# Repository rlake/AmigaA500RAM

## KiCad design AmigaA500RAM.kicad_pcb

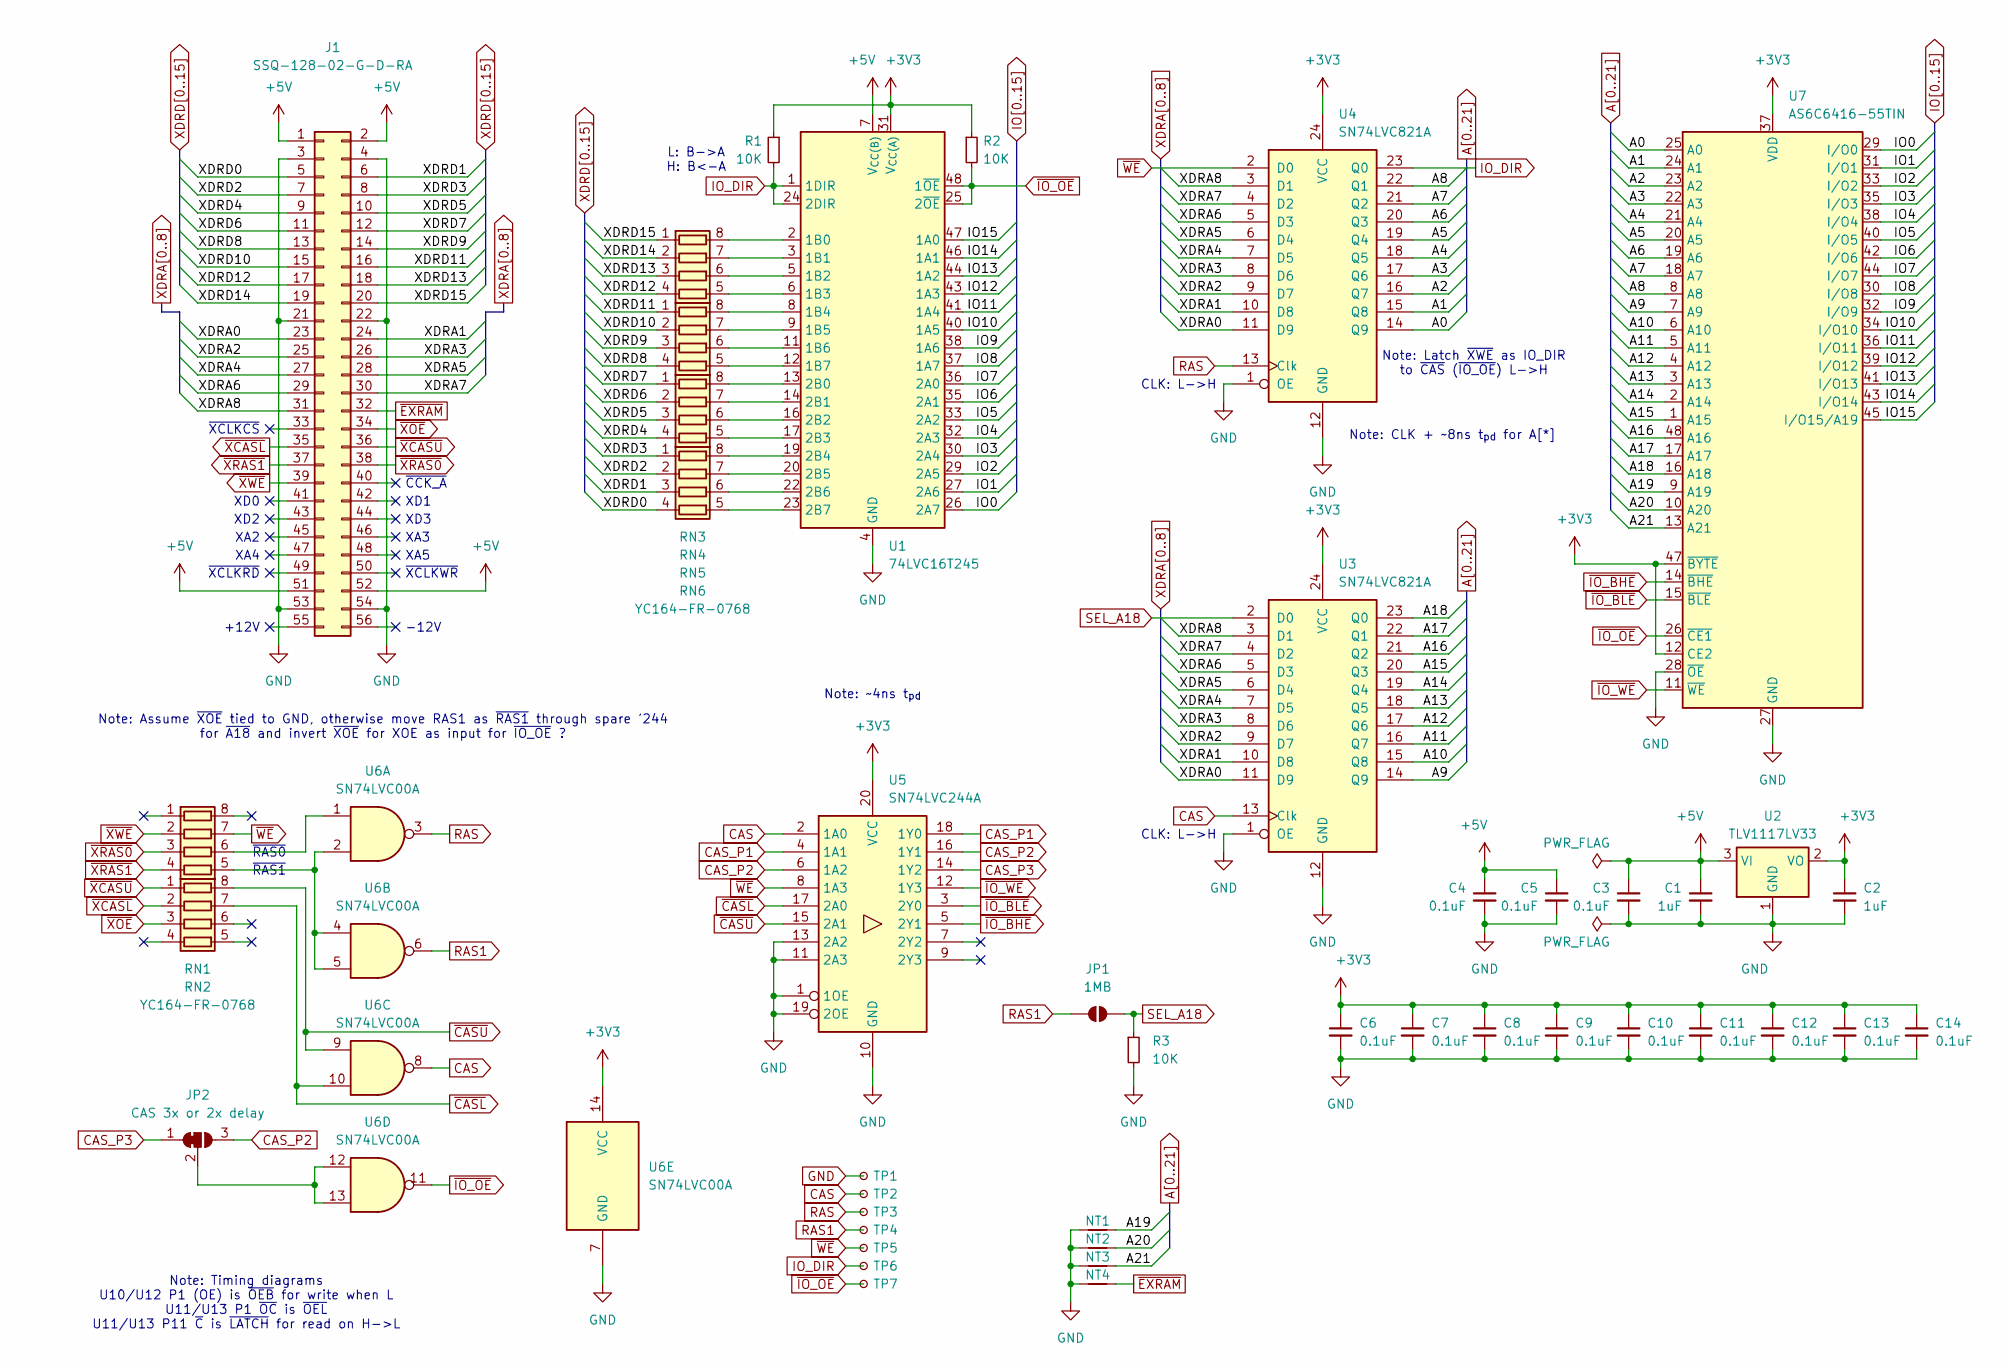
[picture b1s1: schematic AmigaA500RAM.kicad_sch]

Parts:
C1, C2: 1uF; C_0805_2012Metric
C3, C4, C5, C6, C7, C8, C9, C10, C11, C12, C13, C14: 0.1uF; C_0805_2012Metric
J1: SSQ-128-02-G-D-RA; PinSocket_2x28_P2.54mm_Horizontal_A501
JP1: 1MB; SolderJumper-2_P1.3mm_Open_RoundedPad1.0x1.5mm
JP2: CAS 3x or 2x delay; SolderJumper-3_P1.3mm_Bridged2Bar12_RoundedPad1.0x1.5mm
NT1, NT2, NT3, NT4: NetTie_2; NetTie-2_SMD_Pad0.5mm
R1, R2, R3: 10K; R_0805_2012Metric
RN1, RN2, RN3, RN4, RN5, RN6: YC164-FR-0768; R_Array_Convex_4x0603
TP1: TestPoint_Small; TestPoint_Keystone_5016_Compact
TP2, TP3, TP4, TP5, TP6, TP7: TestPoint_Small; TestPoint_Pad_D1.0mm
U1: 74LVC16T245; TSSOP-48_6.1x12.5mm_P0.5mm
U2: TLV1117LV33; SOT-223-3_TabPin2
U3, U4: SN74LVC821A; TSSOP-24_4.4x7.8mm_P0.65mm
U5: SN74LVC244A; TSSOP-20_4.4x6.5mm_P0.65mm
U6: SN74LVC00A; TSSOP-14_4.4x5mm_P0.65mm
U7: AS6C6416-55TIN; TSOP-I-48_18.4x12mm_P0.5mm

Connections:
+3V3: C2.1, C6.1, C7.1, C8.1, C9.1, C10.1, C11.1, C12.1, C13.1, C14.1, R1.1, R2.1, U1.31 (V_{CC(A)}), U1.42 (V_{CC(A)}), U2.2 (VO), U3.24 (VCC), U4.24 (VCC), U5.20 (VCC), U6.14 (VCC), U7.12 (CE2), U7.37 (VDD), U7.47 (~BYTE)
+5V: C1.1, C3.1, C4.1, C5.1, J1.1, J1.2, J1.51, J1.52, U1.7 (V_{CC(B)}), U1.18 (V_{CC(B)}), U2.3 (VI)
A0: U4.14 (Q9), U7.25 (A0)
A1: U4.15 (Q8), U7.24 (A1)
A2: U4.16 (Q7), U7.23 (A2)
A3: U4.17 (Q6), U7.22 (A3)
A4: U4.18 (Q5), U7.21 (A4)
A5: U4.19 (Q4), U7.20 (A5)
A6: U4.20 (Q3), U7.19 (A6)
A7: U4.21 (Q2), U7.18 (A7)
A8: U4.22 (Q1), U7.8 (A8)
A9: U3.14 (Q9), U7.7 (A9)
A10: U3.15 (Q8), U7.6 (A10)
A11: U3.16 (Q7), U7.5 (A11)
A12: U3.17 (Q6), U7.4 (A12)
A13: U3.18 (Q5), U7.3 (A13)
A14: U3.19 (Q4), U7.2 (A14)
A15: U3.20 (Q3), U7.1 (A15)
A16: U3.21 (Q2), U7.48 (A16)
A17: U3.22 (Q1), U7.17 (A17)
A18: U3.23 (Q0), U7.16 (A18)
A19: NT1.2, U7.9 (A19)
A20: NT2.2, U7.10 (A20)
A21: NT3.2, U7.13 (A21)
CAS: TP2.1, U3.13 (Clk), U5.2 (1A0), U6.8
CAS_P1: U5.4 (1A1), U5.18 (1Y0)
CAS_P2: JP2.3 (B), U5.6 (1A2), U5.16 (1Y1)
CAS_P3: JP2.1 (A), U5.14 (1Y2)
GND: C1.2, C2.2, C3.2, C4.2, C5.2, C6.2, C7.2, C8.2, C9.2, C10.2, C11.2, C12.2, C13.2, C14.2, J1.3, J1.4, J1.21, J1.22, J1.53, J1.54, NT1.1, NT2.1, NT3.1, NT4.1, R3.2, TP1.1, U1.4 (GND), U1.10 (GND), U1.15 (GND), U1.21 (GND), U1.28 (GND), U1.34 (GND), U1.39 (GND), U1.45 (GND), U2.1 (GND), U3.1 (OE), U3.12 (GND), U4.1 (OE), U4.12 (GND), U5.1 (1OE), U5.10 (GND), U5.11 (2A3), U5.13 (2A2), U5.19 (2OE), U6.7 (GND), U7.27 (GND), U7.28 (~OE), U7.46 (GND)
IO0: U1.26 (2A7), U7.29 (I/O0)
IO1: U1.27 (2A6), U7.31 (I/O1)
IO2: U1.29 (2A5), U7.33 (I/O2)
IO3: U1.30 (2A4), U7.35 (I/O3)
IO4: U1.32 (2A3), U7.38 (I/O4)
IO5: U1.33 (2A2), U7.40 (I/O5)
IO6: U1.35 (2A1), U7.42 (I/O6)
IO7: U1.36 (2A0), U7.44 (I/O7)
IO8: U1.37 (1A7), U7.30 (I/O8)
IO9: U1.38 (1A6), U7.32 (I/O9)
IO10: U1.40 (1A5), U7.34 (I/O10)
IO11: U1.41 (1A4), U7.36 (I/O11)
IO12: U1.43 (1A3), U7.39 (I/O12)
IO13: U1.44 (1A2), U7.41 (I/O13)
IO14: U1.46 (1A1), U7.43 (I/O14)
IO15: U1.47 (1A0), U7.45 (I/O15/A19)
IO_DIR: R1.2, TP6.1, U1.1 (1DIR), U1.24 (2DIR), U4.23 (Q0)
unnamed: JP2.2 (C), U6.12, U6.13
unnamed 47: RN1.6 (R3.2), U6.1; also elsewhere on the board
unnamed 48: RN1.5 (R4.2), U6.2, U6.4, U6.5; also elsewhere on the board
unnamed 49: RN3.8 (R1.2), U1.2 (1B0); also elsewhere on the board
unnamed 50: RN3.7 (R2.2), U1.3 (1B1); also elsewhere on the board
unnamed 51: RN3.6 (R3.2), U1.5 (1B2); also elsewhere on the board
unnamed 52: RN3.5 (R4.2), U1.6 (1B3); also elsewhere on the board
unnamed: RN4.8 (R1.2), U1.8 (1B4)
unnamed: RN4.7 (R2.2), U1.9 (1B5)
unnamed: RN4.6 (R3.2), U1.11 (1B6)
unnamed: RN4.5 (R4.2), U1.12 (1B7)
unnamed: RN5.8 (R1.2), U1.13 (2B0)
unnamed: RN5.7 (R2.2), U1.14 (2B1)
unnamed: RN5.6 (R3.2), U1.16 (2B2)
unnamed: RN5.5 (R4.2), U1.17 (2B3)
unnamed: RN6.8 (R1.2), U1.19 (2B4)
unnamed: RN6.7 (R2.2), U1.20 (2B5)
unnamed: RN6.6 (R3.2), U1.22 (2B6)
unnamed: RN6.5 (R4.2), U1.23 (2B7)
RAS: TP3.1, U4.13 (Clk), U6.3
RAS1: JP1.1 (A), TP4.1, U6.6
SEL_A18: JP1.2 (B), R3.1, U3.2 (D0)
XDRA0: J1.23, U3.11 (D9), U4.11 (D9)
XDRA1: J1.24, U3.10 (D8), U4.10 (D8)
XDRA2: J1.25, U3.9 (D7), U4.9 (D7)
XDRA3: J1.26, U3.8 (D6), U4.8 (D6)
XDRA4: J1.27, U3.7 (D5), U4.7 (D5)
XDRA5: J1.28, U3.6 (D4), U4.6 (D4)
XDRA6: J1.29, U3.5 (D3), U4.5 (D3)
XDRA7: J1.30, U3.4 (D2), U4.4 (D2)
XDRA8: J1.31, U3.3 (D1), U4.3 (D1)
XDRD0: J1.5, RN6.4 (R4.1)
XDRD1: J1.6, RN6.3 (R3.1)
XDRD2: J1.7, RN6.2 (R2.1)
XDRD3: J1.8, RN6.1 (R1.1)
XDRD4: J1.9, RN5.4 (R4.1)
XDRD5: J1.10, RN5.3 (R3.1)
XDRD6: J1.11, RN5.2 (R2.1)
XDRD7: J1.12, RN5.1 (R1.1)
XDRD8: J1.13, RN4.4 (R4.1)
XDRD9: J1.14, RN4.3 (R3.1)
XDRD10: J1.15, RN4.2 (R2.1)
XDRD11: J1.16, RN4.1 (R1.1)
XDRD12: J1.17, RN3.4 (R4.1); also elsewhere on the board
XDRD13: J1.18, RN3.3 (R3.1); also elsewhere on the board
XDRD14: J1.19, RN3.2 (R2.1); also elsewhere on the board
XDRD15: J1.20, RN3.1 (R1.1); also elsewhere on the board
~CASL: RN2.7 (R2.2), U5.17 (2A0), U6.10
~CASU: RN2.8 (R1.2), U5.15 (2A1), U6.9
~EXRAM: J1.32, NT4.2
~IO_BHE: U5.5 (2Y1), U7.14 (~BHE)
~IO_BLE: U5.3 (2Y0), U7.15 (~BLE)
~IO_OE: R2.2, TP7.1, U1.25 (2~OE), U1.48 (1~OE), U6.11, U7.26 (~CE1)
~IO_WE: U5.12 (1Y3), U7.11 (~WE)
~WE: RN1.7 (R2.2), TP5.1, U4.2 (D0), U5.8 (1A3); also elsewhere on the board
~XCASL: J1.35, RN2.2 (R2.1)
~XCASU: J1.36, RN2.1 (R1.1)
~XOE: J1.34, RN2.3 (R3.1)
~XRAS0: J1.38, RN1.3 (R3.1); also elsewhere on the board
~XRAS1: J1.37, RN1.4 (R4.1); also elsewhere on the board
~XWE: J1.39, RN1.2 (R2.1); also elsewhere on the board

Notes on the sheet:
XA3
+12V
~{CCK_A}
Note: ~4ns t_{pd}
Note: Timing diagrams U10/U12 P1 (OE) is ~{OEB} for write when L U11/U13 P1 ~{OC} is ~{OEL} U11/U13 P11 ~{C} is ~{LATCH} for read on H->L
XA4
XA5
Note: CLK + ~8ns t_{pd} for A[*]
XD1
~{XCLKRD}
Note: Assume ~{XOE} tied to GND, otherwise move RAS1 as ~{RAS1} through spare '244 for ~{A18} and invert ~{XOE} for XOE as input for ~{IO_OE} ?
~{RAS0}
-12V
XD0
XD2
Note: Latch ~{XWE} as IO_DIR to ~{CAS} (~{IO_OE}) L->H
CLK: L->H
XD3
~{RAS1}
L: B->A H: B<-A
~{XCLKCS}
XA2
~{XCLKWR}

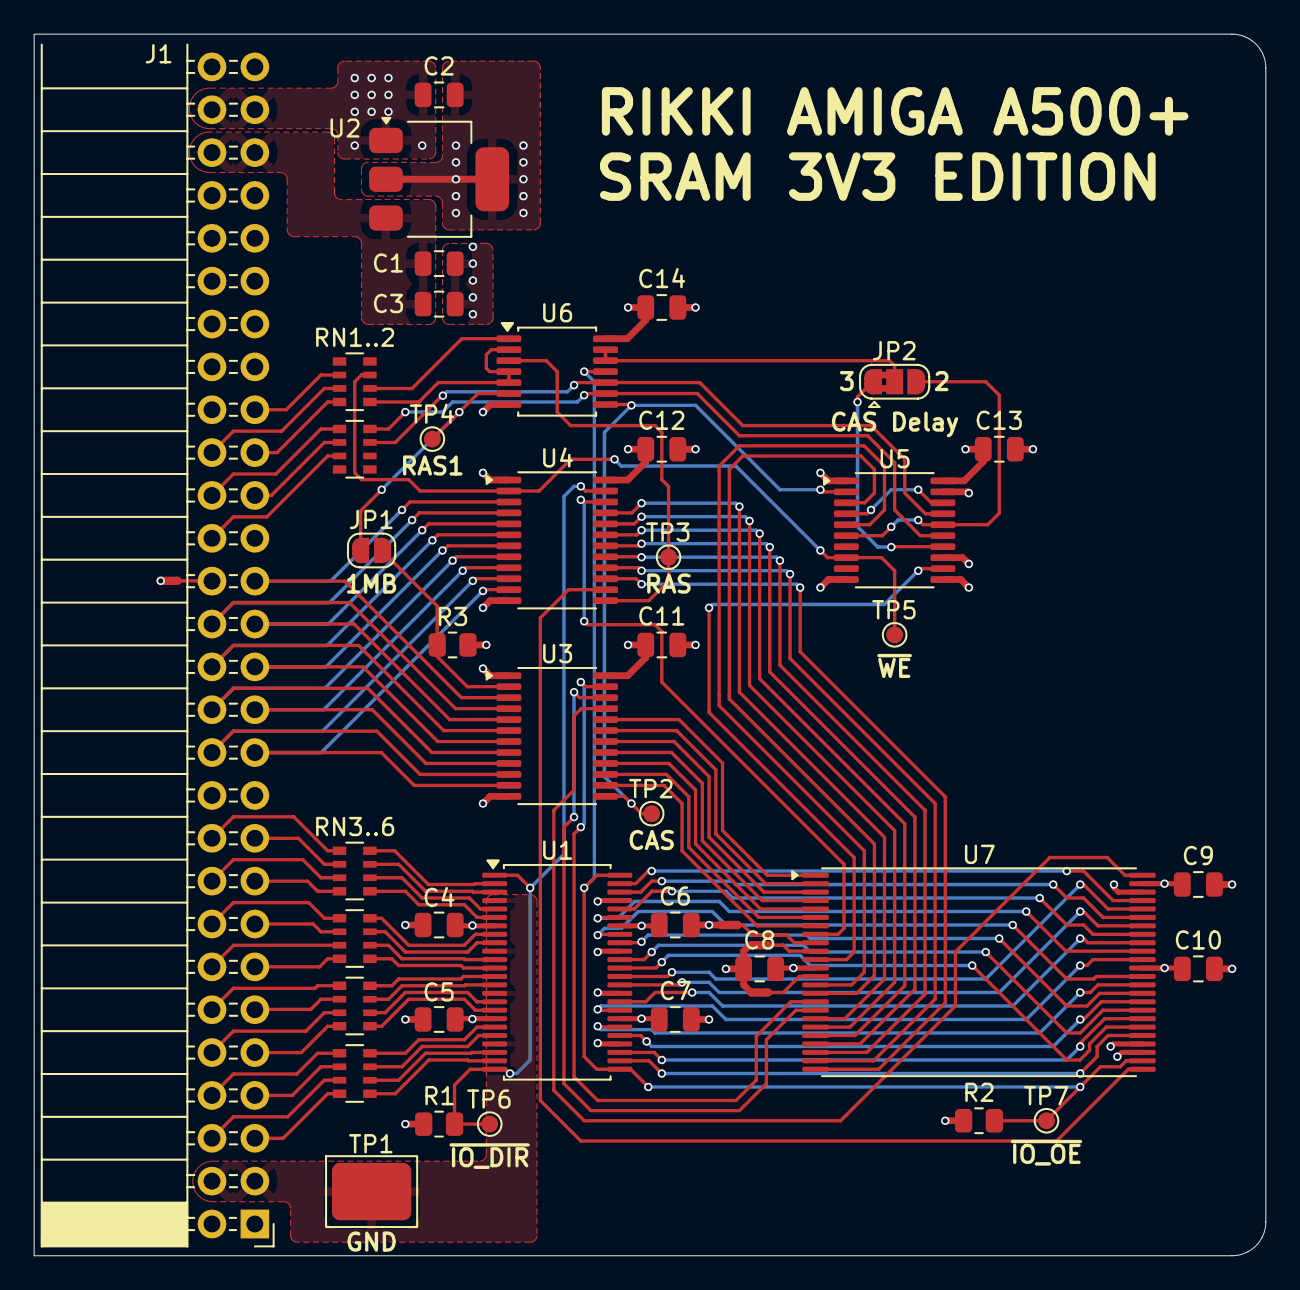
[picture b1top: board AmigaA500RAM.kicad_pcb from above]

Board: 4 copper layers, 73.0 x 72.4 mm, 44 parts (0 on the bottom side), 107 nets.

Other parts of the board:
RN1..2, RN3..6: YC164-FR-0768; R_Array_Convex_4x0603

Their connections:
unnamed 47: RN1..2.6 (R3.2); also elsewhere on the board
unnamed 48: RN1..2.5 (R4.2); also elsewhere on the board
unnamed 49: RN3..6.8 (R1.2); also elsewhere on the board
unnamed 50: RN3..6.7 (R2.2); also elsewhere on the board
unnamed 51: RN3..6.6 (R3.2); also elsewhere on the board
unnamed 52: RN3..6.5 (R4.2); also elsewhere on the board
XDRD12: RN3..6.4 (R4.1); also elsewhere on the board
XDRD13: RN3..6.3 (R3.1); also elsewhere on the board
XDRD14: RN3..6.2 (R2.1); also elsewhere on the board
XDRD15: RN3..6.1 (R1.1); also elsewhere on the board
~WE: RN1..2.7 (R2.2); also elsewhere on the board
~XRAS0: RN1..2.3 (R3.1); also elsewhere on the board
~XRAS1: RN1..2.4 (R4.1); also elsewhere on the board
~XWE: RN1..2.2 (R2.1); also elsewhere on the board

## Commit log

2026-01-14 Initial KiCad project
2026-01-24 Add symbols for SRAM, flip-flop and regulator
2026-01-24 Add footprints for connector, resistor array, test
2026-01-24 Amiga A500 RAM Schematic
2026-01-24 Amiga A500 RAM PCB
2026-01-24 Amiga A500 RAM BOM
2026-01-24 Amiga A500 RAM PCB Render
2026-01-29 Update resistor arrays to 4x0603
